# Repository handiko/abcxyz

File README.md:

# abcxyz
Random stuff from a to z

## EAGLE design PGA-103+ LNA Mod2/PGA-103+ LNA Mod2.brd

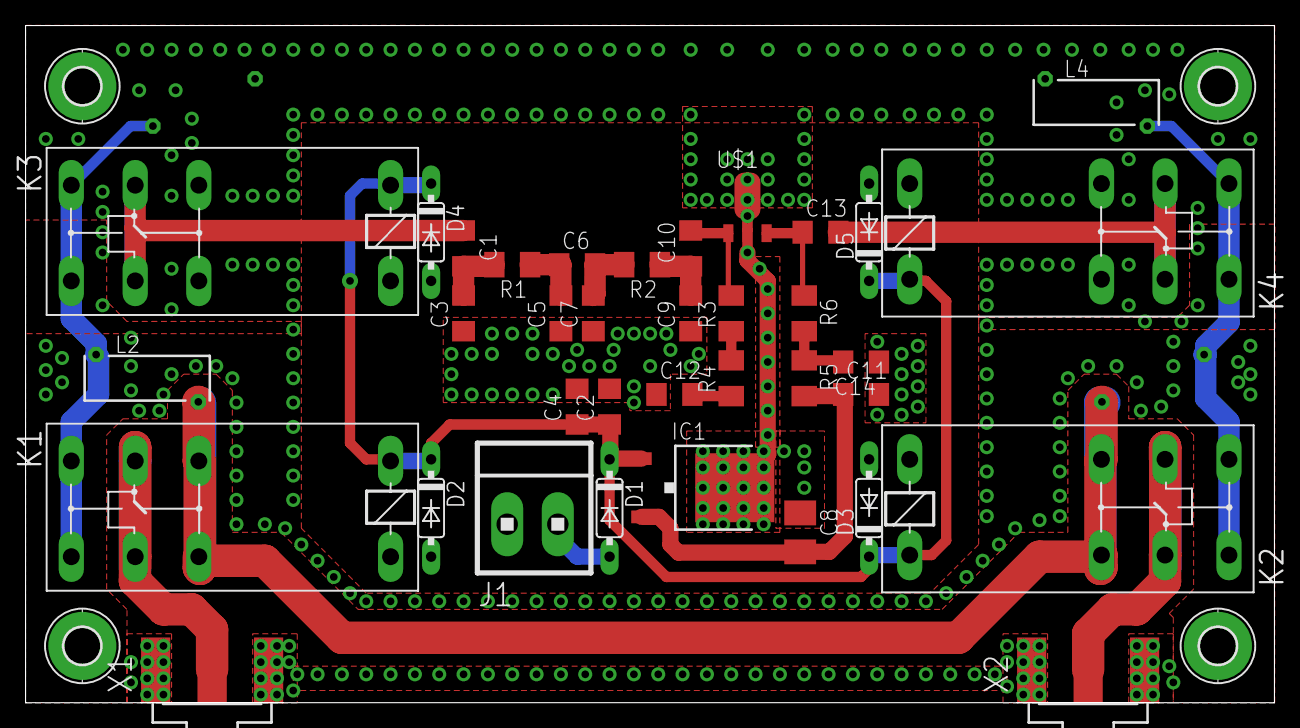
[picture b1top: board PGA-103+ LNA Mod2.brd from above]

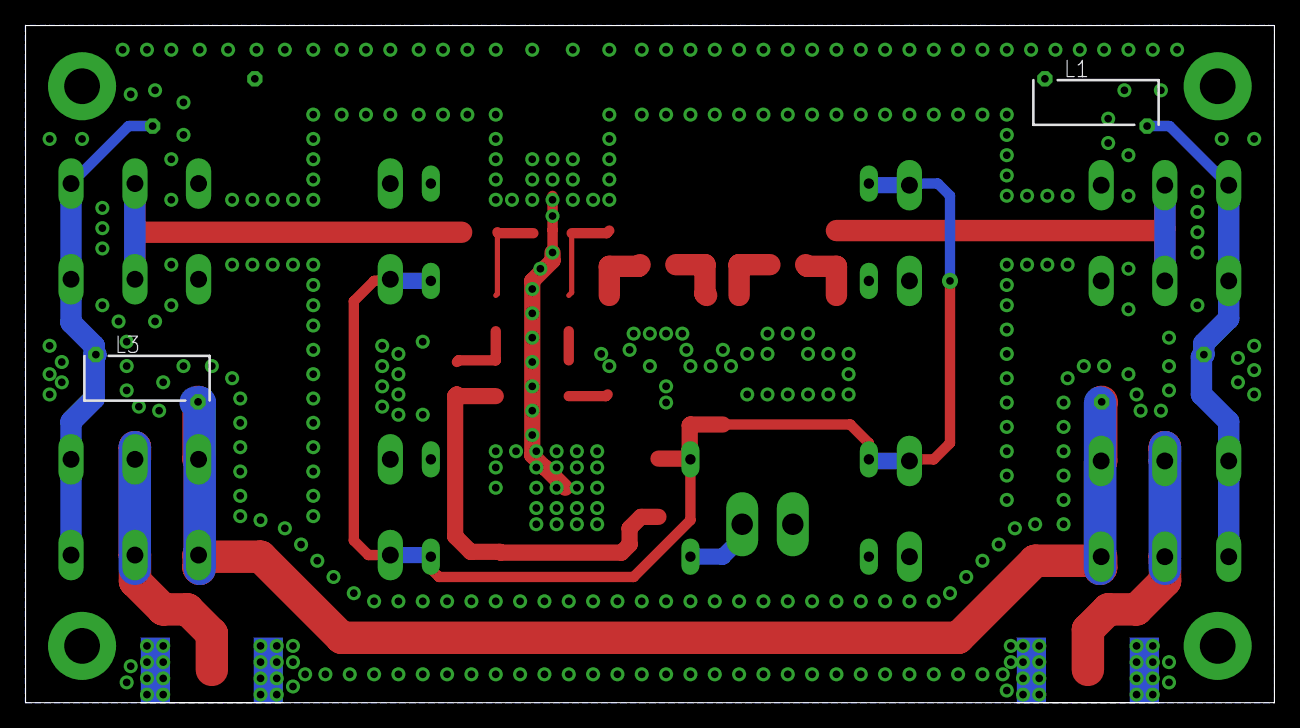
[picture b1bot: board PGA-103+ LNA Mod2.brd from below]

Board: 2 copper layers, 97.8 x 53.0 mm, 42 parts (2 on the bottom side), 20 nets.

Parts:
C1, C6, C10, C13: 10n; C1206
C2, C4, C11, C14: 1n; C1206
C3, C5, C7, C9, C12: 330p; C1206
C8: 10u; B/3528-21R
D1, D2, D3, D4, D5: 1N4xxx; DO35-7
H1, H2, H3, H4: MOUNT-PAD; 2,8-PAD
IC1: 7805DT; TO252
J1: 1X2MTA
K1, K2, K3, K4: G2RE
L1, L2, L3, L4: Z28/7
R1, R2, R3, R6: 1u; M1206
R4: 150; M1206
R5: 22; M1206
U$1: PGA-103; DF782
X1, X2: SMA; J502-ND-142-0701-851/861

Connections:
ANT: K1.P0, K1.P1, X1.1
GND: C2.2, C3.1, C4.2, C5.1, C7.1, C8.-, C9.1, C11.2, C12.1, C14.1, D2.A, D3.A, D4.A, D5.A, H1.B2,8, H2.B2,8, H3.B2,8, H4.B2,8, IC1.3, J1.2, K1.2, K2.2, K3.2, K3.O0, K3.O1, K4.2, K4.O0, K4.O1, L1.2, L4.2, U$1.GND-1, U$1.GND-2, X1.G@1, X1.G@2, X1.G@3, X1.G@4, X2.G@1, X2.G@2, X2.G@3, X2.G@4
LNA_IN: C1.1, K3.P0, K3.P1
LNA_OUT: C13.2, K4.P0, K4.P1
unnamed: C10.2, R3.2, U$1.RF-IN
unnamed: C13.1, R6.1, U$1.RF-OUT
unnamed: C8.+, C11.1, IC1.2, R5.2
unnamed: D1.A, J1.1
unnamed: C9.2, C10.1, R2.1
unnamed: C14.2, R5.1, R6.2
unnamed: R3.1, R4.2
unnamed: C12.2, R4.1
unnamed: C6.2, C7.2, R2.2
unnamed: C5.2, C6.1, R1.1
unnamed: C1.2, C3.2, R1.2
unnamed: K1.S0, K1.S1, K3.S0, K3.S1, L1.1, L2.2
unnamed: K2.S0, K2.S1, K4.S0, K4.S1, L3.2, L4.1
RF_BYPASS: K1.O0, K1.O1, K2.O0, K2.O1, L2.1, L3.1
TRX: K2.P0, K2.P1, X2.1
VCC: C2.1, C4.1, D1.C, D2.C, D3.C, D4.C, D5.C, IC1.1, K1.1, K2.1, K3.1, K4.1

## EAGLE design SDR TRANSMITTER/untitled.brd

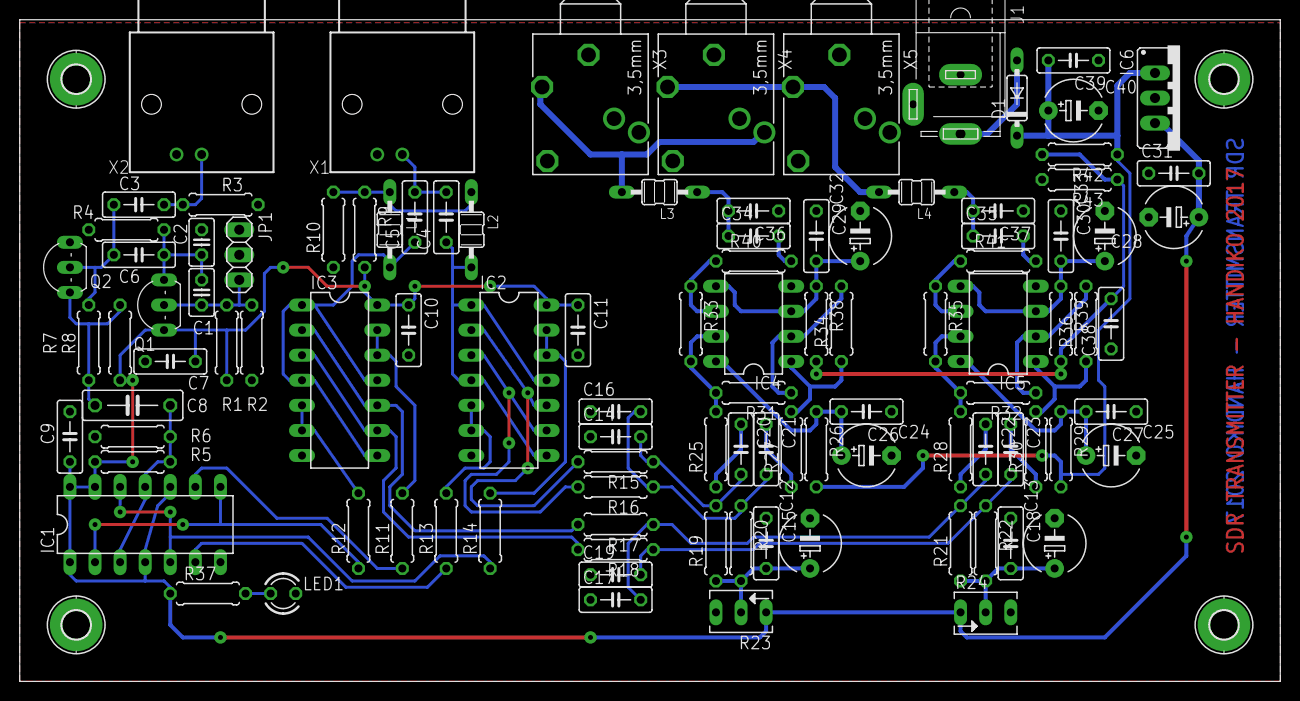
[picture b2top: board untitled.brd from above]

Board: 2 copper layers, 127.6 x 67.0 mm, 108 parts (0 on the bottom side), 56 nets.

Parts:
C1, C2: 22; C025-025X050
C3, C4, C5, C6, C15, C18, C20, C21, C22, C23, C26, C27, C29, C30, C31, C34, C35, C36, C37, C38, C39: C050-025X075
C7, C9, C10, C11: 10n; C050-025X075
C8: 100n; C075-032X103
C12, C13, C24, C25, C28, C32, C33, C40: E5-6
C14, C16, C17, C19: 1n; C050-025X075
D1: 1N4148DO35-7; DO35-7
H1, H2, H3, H4: MOUNT-PAD-ROUND2.8; 2,8-PAD
IC1: 74AC74N; DIL14
IC2, IC3: 4066N; DIL14
IC4, IC5: NE5532; DIL08
IC6: 78XXS
J1: SPC4077
JP1: 1X03
L1, L2, L3, L4: 3u9; MMICC7
LED1: LED3MM
Q1, Q2: BC548; TO92-EBC
R1, R2, R8, R31, R32, R33, R34, R35, R36: 10k; 0207/7
R3: 0207/7
R4: 680; 0207/7
R5, R6, R7: 100k; 0207/7
R9, R10: 2k2; 0207/7
R11, R12, R13, R14: 47; 0207/7
R15, R16, R17, R18: 10; 0207/7
R19, R20, R21, R22, R40, R41, R42, R43: 1k; 0207/7
R23, R24: B64Y
R25, R27, R28, R30: 220; 0207/7
R26, R29, R38, R39: 100; 0207/7
R37: 330; 0207/7
X1, X2: 227161-8; AMP_227161
X3, X4, X5: PG203J

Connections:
+5V: C7.2, C9.1, C10.1, C11.1, C28.+, C31.2, IC1.1, IC1.4, IC1.10, IC1.13, IC1.14, IC2.14, IC3.14, IC6.OUT, Q1.C, R1.1, R5.1, R8.1, R9.2, R23.E, R24.E, R37.1
+12V: C39.2, C40.+, D1.C, IC6.IN, R26.2, R29.2, R42.1
+24V: C38.2, R38.2, R39.2, R42.2, R43.1
GND: C2.2, C7.1, C9.2, C10.2, C11.2, C12.-, C13.-, C14.1, C15.1, C16.1, C17.1, C18.1, C19.1, C24.-, C25.-, C26.1, C27.1, C28.-, C29.1, C30.1, C31.1, C32.-, C33.-, C36.1, C37.1, C38.1, C39.1, C40.-, H1.B2,8, H2.B2,8, H3.B2,8, H4.B2,8, IC1.7, IC2.7, IC3.7, IC4.4, IC5.4, IC6.GND, J1.1, J1.2, JP1.1, LED1.K, Q2.E, R2.2, R3.2, R4.2, R6.2, R10.1, R23.A, R24.A, R43.2, X1.2, X2.2, X3.1, X4.1, X5.1
unnamed: L1.1, L2.1, R9.1, R10.2
unnamed: C4.2, C5.2, X1.1
unnamed: C4.1, IC2.1, IC2.4, IC2.8, IC2.11, L2.2
unnamed: C5.1, IC3.1, IC3.4, IC3.8, IC3.11, L1.2
unnamed: IC2.3, IC2.9, R16.2
unnamed: IC2.2, IC2.10, R15.2
unnamed: IC3.2, IC3.10, R17.2
unnamed: IC3.3, IC3.9, R18.2
unnamed: IC2.12, IC2.13, R14.2
unnamed: IC2.5, IC2.6, R13.2
unnamed: IC3.12, IC3.13, R11.2
unnamed: IC3.5, IC3.6, R12.2
unnamed: C14.2, C20.2, R15.1, R19.2
unnamed: C16.2, C21.2, R16.1, R20.1
unnamed: C17.2, C22.2, R17.1, R21.2
unnamed: C19.2, C23.2, R18.1, R22.1
unnamed: IC1.2, IC1.8, R12.1
unnamed: IC1.6, R13.1
unnamed: IC1.5, IC1.12, R14.1
unnamed: IC1.9, R11.1
unnamed: C8.1, IC1.3, IC1.11, R5.2, R6.1
unnamed: IC4.1, R27.2, R34.1
unnamed: C21.1, R27.1
unnamed: C20.1, R25.1
unnamed: IC4.7, R25.2, R31.2, R33.2
unnamed: IC4.2, R31.1, R34.2
unnamed: IC4.6, R33.1, R40.1
unnamed: C24.+, C26.2, IC4.8, R26.1
unnamed: C29.2, C32.+, IC4.3, IC4.5, R38.1
unnamed: C34.2, R40.2
unnamed: C34.1, C36.2, L3.1
unnamed: C12.+, C15.2, R19.1, R20.2, R23.S
unnamed: D1.A, J1.3
unnamed: C3.1, R3.1, X2.1
unnamed: IC5.1, R30.2, R36.1
unnamed: C23.1, R30.1
unnamed: C22.1, R28.1
unnamed: IC5.7, R28.2, R32.2, R35.2
unnamed: IC5.2, R32.1, R36.2
unnamed: IC5.6, R35.1, R41.1
unnamed: C25.+, C27.2, IC5.8, R29.1
unnamed: C35.2, R41.2
unnamed: C30.2, C33.+, IC5.3, IC5.5, R39.1
unnamed: C35.1, C37.2, L4.1
unnamed: C13.+, C18.2, R21.1, R22.2, R24.S
unnamed: C1.1, JP1.3, Q1.B, R1.2, R2.1
unnamed: C1.2, C2.1, C6.2, Q1.E, R4.1
unnamed: L3.2, X3.5, X4.2
unnamed: C8.2, Q2.C, R7.2, R8.2
unnamed: C3.2, C6.1, Q2.B, R7.1
unnamed: LED1.A, R37.2
unnamed: L4.2, X4.5, X5.5

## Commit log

2018-09-26 Adding bypass cap
2018-09-26 Modified
2018-09-27 Adding V1
2018-10-28 Create LICENSE
